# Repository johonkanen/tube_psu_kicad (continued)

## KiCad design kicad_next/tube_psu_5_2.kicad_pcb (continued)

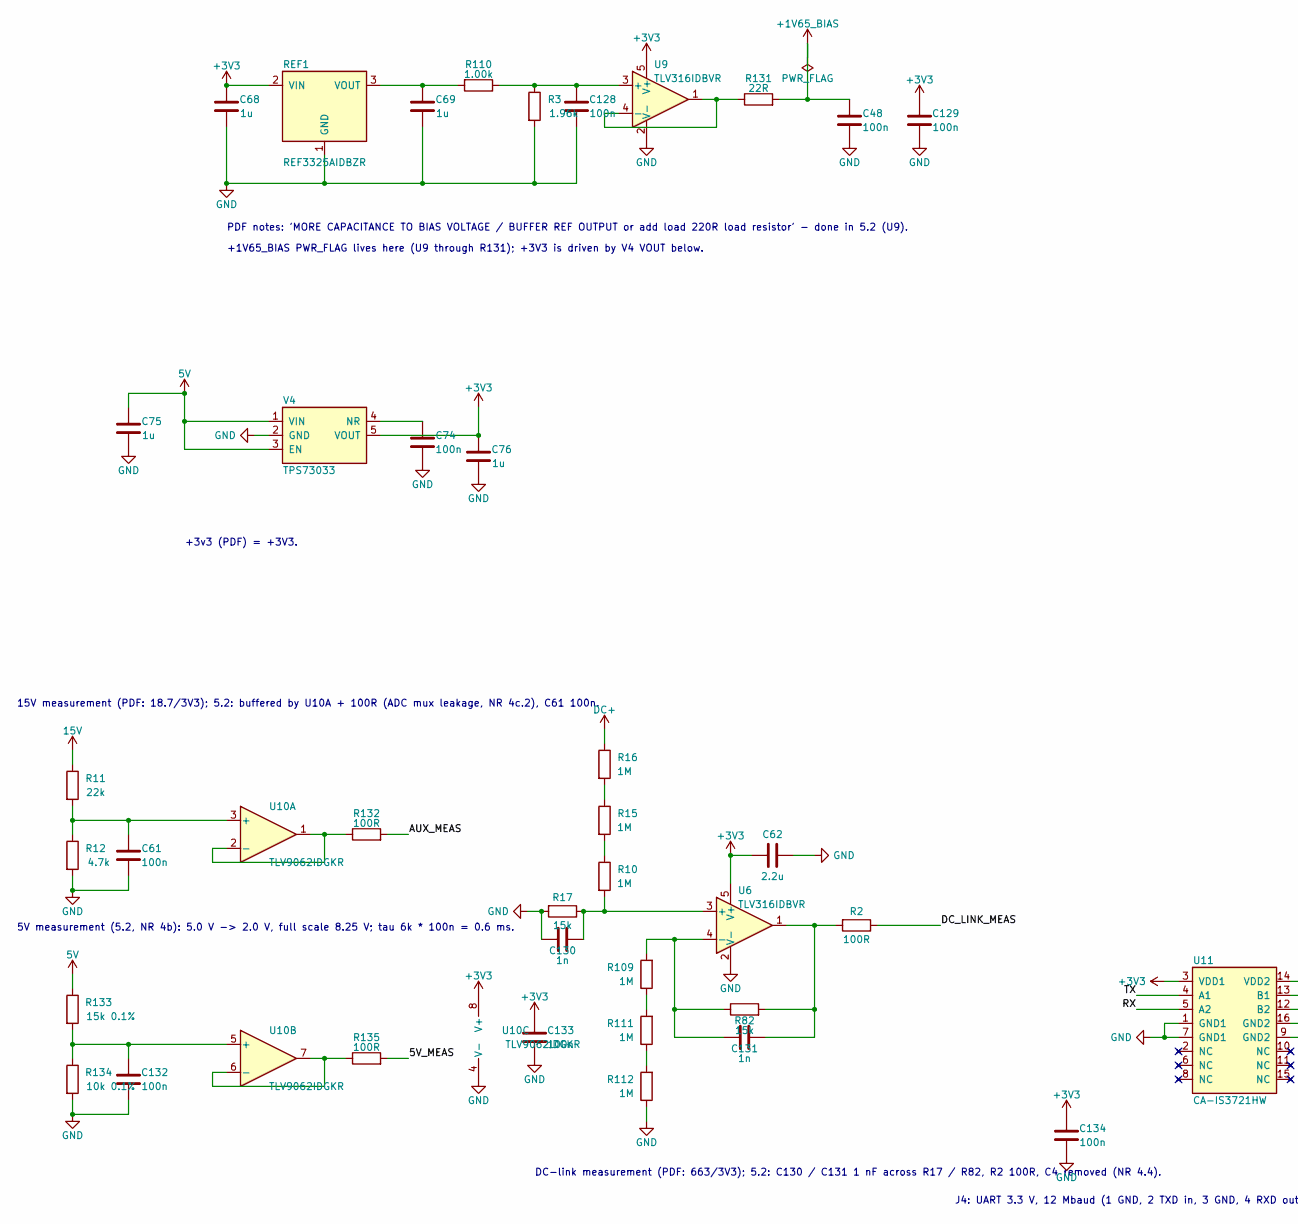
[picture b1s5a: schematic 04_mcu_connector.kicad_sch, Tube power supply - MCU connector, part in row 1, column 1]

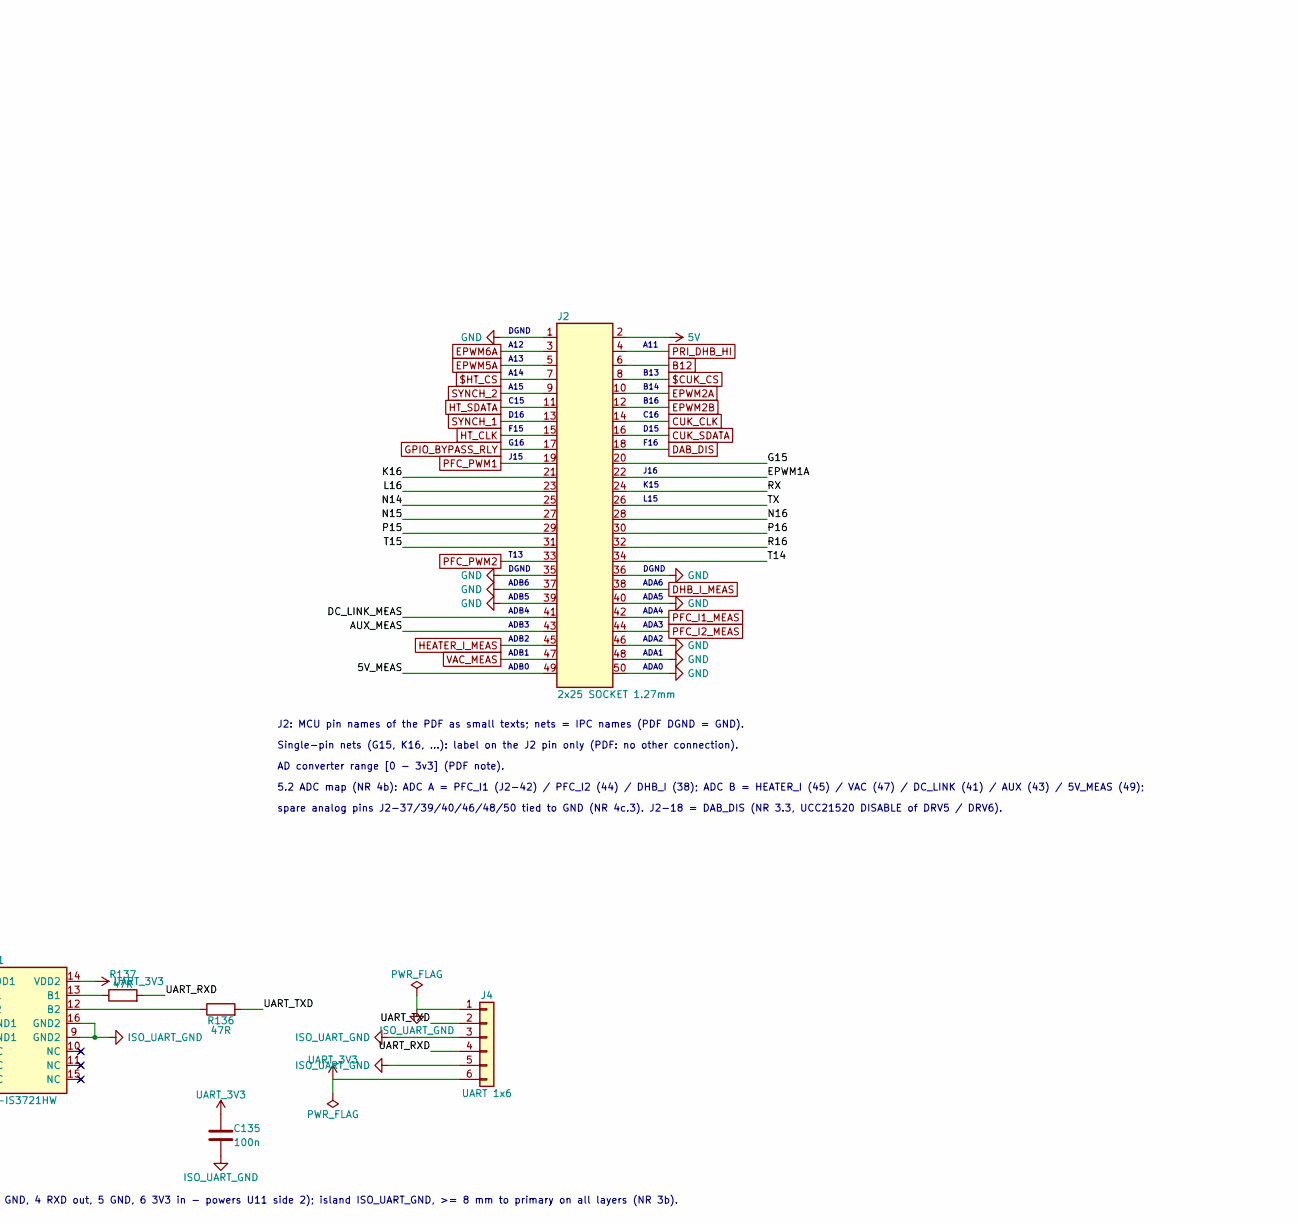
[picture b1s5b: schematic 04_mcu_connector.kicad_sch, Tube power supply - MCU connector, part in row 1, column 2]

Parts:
C48, C61, C74, C128, C129, C132, C133, C134, C135: 100n; C_0603_1608Metric; LCSC C14663
C62: 2.2u; C_0603_1608Metric; LCSC C23630
C68, C69, C75, C76: 1u; C_0603_1608Metric; LCSC C15849
C130, C131: 1n; C_0603_1608Metric; LCSC C106246
J2: 2x25 SOCKET 1.27mm; PinSocket_2x25_P1.27mm_Vertical_XKB_X1321FV; LCSC C2881768
J4: UART 1x6; PinHeader_1x06_P2.54mm_Vertical; LCSC C492405
R2, R132, R135: 100R; R_0603_1608Metric; LCSC C22775
R3: 1.96k; R_0603_1608Metric; LCSC C22854
R10, R15, R16, R111, R112: 1M; R_0805_2012Metric_Pad1.20x1.40mm_HandSolder; LCSC C17514
R11: 22k; R_0603_1608Metric; LCSC C31850
R12: 4.7k; R_0603_1608Metric; LCSC C23162
R17, R82: 15k; R_0603_1608Metric; LCSC C22809
R109: 1M; R_0805_2012Metric_Proteus; LCSC C17514
R110: 1.00k; R_0603_1608Metric; LCSC C21190
R131: 22R; R_0603_1608Metric; LCSC C23345
R133: 15k 0.1%; R_0603_1608Metric; LCSC C318137
R134: 10k 0.1%; R_0603_1608Metric; LCSC C95204
R136, R137: 47R; R_0603_1608Metric; LCSC C23182
REF1: REF3325AIDBZR; SOT-23_Proteus; LCSC C69039
U6: TLV316IDBVR; SOT-23-5_Proteus; LCSC C575578
U9: TLV316IDBVR; SOT-23-5; LCSC C575578
U10: TLV9062IDGKR; VSSOP-8_3x3mm_P0.65mm; LCSC C398356
U11: CA-IS3721HW; SOIC-16W_7.5x10.3mm_P1.27mm_Slot8.0; LCSC C5337993
V4: TPS73033; SOT-23-5_Proteus; LCSC C57424

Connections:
5V: C75.1, J2.2, R133.1, V4.1 (VIN), V4.3 (EN); also elsewhere on the board
15V: R11.1; also elsewhere on the board
$CUK_CS: J2.8; also elsewhere on the board
$HT_CS: J2.7; also elsewhere on the board
+1V65_BIAS: C48.1, R131.2; also elsewhere on the board
+3V3: C62.1, C68.1, C76.1, C129.1, C133.1, C134.1, REF1.2 (VIN), U6.5 (V+), U9.5 (V+), U10.8 (V+), U11.3 (VDD1), V4.5 (VOUT); also elsewhere on the board
/04 MCU connector/5V_MEAS: J2.49, R135.2
/04 MCU connector/AUX_MEAS: J2.43, R132.2
/04 MCU connector/DC_LINK_MEAS: J2.41, R2.1
/04 MCU connector/EPWM1A: J2.22
/04 MCU connector/G15: J2.20
/04 MCU connector/K16: J2.21
/04 MCU connector/L16: J2.23
/04 MCU connector/N14: J2.25
/04 MCU connector/N15: J2.27
/04 MCU connector/N16: J2.28
/04 MCU connector/P15: J2.29
/04 MCU connector/P16: J2.30
/04 MCU connector/R16: J2.32
/04 MCU connector/RX: J2.24, U11.5 (A2)
/04 MCU connector/T14: J2.34
/04 MCU connector/T15: J2.31
/04 MCU connector/TX: J2.26, U11.4 (A1)
/04 MCU connector/UART_RXD: J4.4, R137.2
/04 MCU connector/UART_TXD: J4.2, R136.2
B12: J2.6; also elsewhere on the board
CUK_CLK: J2.14; also elsewhere on the board
CUK_SDATA: J2.16; also elsewhere on the board
DAB_DIS: J2.18; also elsewhere on the board
DC+: R16.1; also elsewhere on the board
DHB_I_MEAS: J2.38; also elsewhere on the board
EPWM2A: J2.10; also elsewhere on the board
EPWM2B: J2.12; also elsewhere on the board
EPWM5A: J2.5; also elsewhere on the board
EPWM6A: J2.3; also elsewhere on the board
GND: C48.2, C61.1, C62.2, C68.2, C69.2, C74.2, C75.2, C76.2, C128.2, C129.2, C130.2, C132.2, C133.2, C134.2, J2.1, J2.35, J2.36, J2.37, J2.39, J2.40, J2.46, J2.48, J2.50, R3.2, R12.2, R17.2, R112.1, R134.2, REF1.1 (GND), U6.2 (V-), U9.2 (V-), U10.4 (V-), U11.1 (GND1), U11.7 (GND1), V4.2 (GND); also elsewhere on the board
GPIO_BYPASS_RLY: J2.17; also elsewhere on the board
HEATER_I_MEAS: J2.45; also elsewhere on the board
HT_CLK: J2.15; also elsewhere on the board
HT_SDATA: J2.11; also elsewhere on the board
ISO_UART_GND: C135.2, J4.1, J4.3, J4.5, U11.9 (GND2), U11.16 (GND2)
unnamed: C131.2, R2.2, R82.2, U6.1
unnamed: R10.1, R15.2
unnamed: R15.1, R16.2
unnamed: R109.1, R111.2
unnamed: R111.1, R112.2
unnamed: C69.1, R110.2, REF1.3 (VOUT)
unnamed: C130.1, R10.2, R17.1, U6.3 (+)
unnamed: C131.1, R82.1, R109.2, U6.4 (-)
unnamed: C128.1, R3.1, R110.1, U9.3 (+)
unnamed: R131.1, U9.1, U9.4 (-)
unnamed: C61.2, R11.2, R12.1, U10.3 (+)
unnamed: R132.1, U10.1, U10.2 (-)
unnamed: C132.1, R133.2, R134.1, U10.5 (+)
unnamed: R135.1, U10.6 (-), U10.7
unnamed: R137.1, U11.13 (B1)
unnamed: R136.1, U11.12 (B2)
unnamed: C74.1, V4.4 (NR)
PFC_I1_MEAS: J2.42; also elsewhere on the board
PFC_I2_MEAS: J2.44; also elsewhere on the board
PFC_PWM1: J2.19; also elsewhere on the board
PFC_PWM2: J2.33; also elsewhere on the board
PRI_DHB_HI: J2.4; also elsewhere on the board
SYNCH_1: J2.13; also elsewhere on the board
SYNCH_2: J2.9; also elsewhere on the board
UART_3V3: C135.1, J4.6, U11.14 (VDD2)
VAC_MEAS: J2.47; also elsewhere on the board

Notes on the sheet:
DGND
A12
A11
A13
A14
B13
A15
B14
C15
B16
D16
C16
F15
D15
G16
F16
J15
J16
K15
L15
T13
ADB6
ADA6
ADB5
ADA5
ADB4
ADA4
ADB3
ADA3
ADB2
ADA2
ADB1
ADA1
ADB0
ADA0
J2: MCU pin names of the PDF as small texts; nets = IPC names (PDF DGND = GND).
Single-pin nets (G15, K16, ...): label on the J2 pin only (PDF: no other connection).
5.2 ADC map (NR 4b): ADC A = PFC_I1 (J2-42) / PFC_I2 (44) / DHB_I (38); ADC B = HEATER_I (45) / VAC (47) / DC_LINK (41) / AUX (43) / 5V_MEAS (49);
spare analog pins J2-37/39/40/46/48/50 tied to GND (NR 4c.3). J2-18 = DAB_DIS (NR 3.3, UCC21520 DISABLE of DRV5 / DRV6).
AD converter range [0 - 3v3] (PDF note).

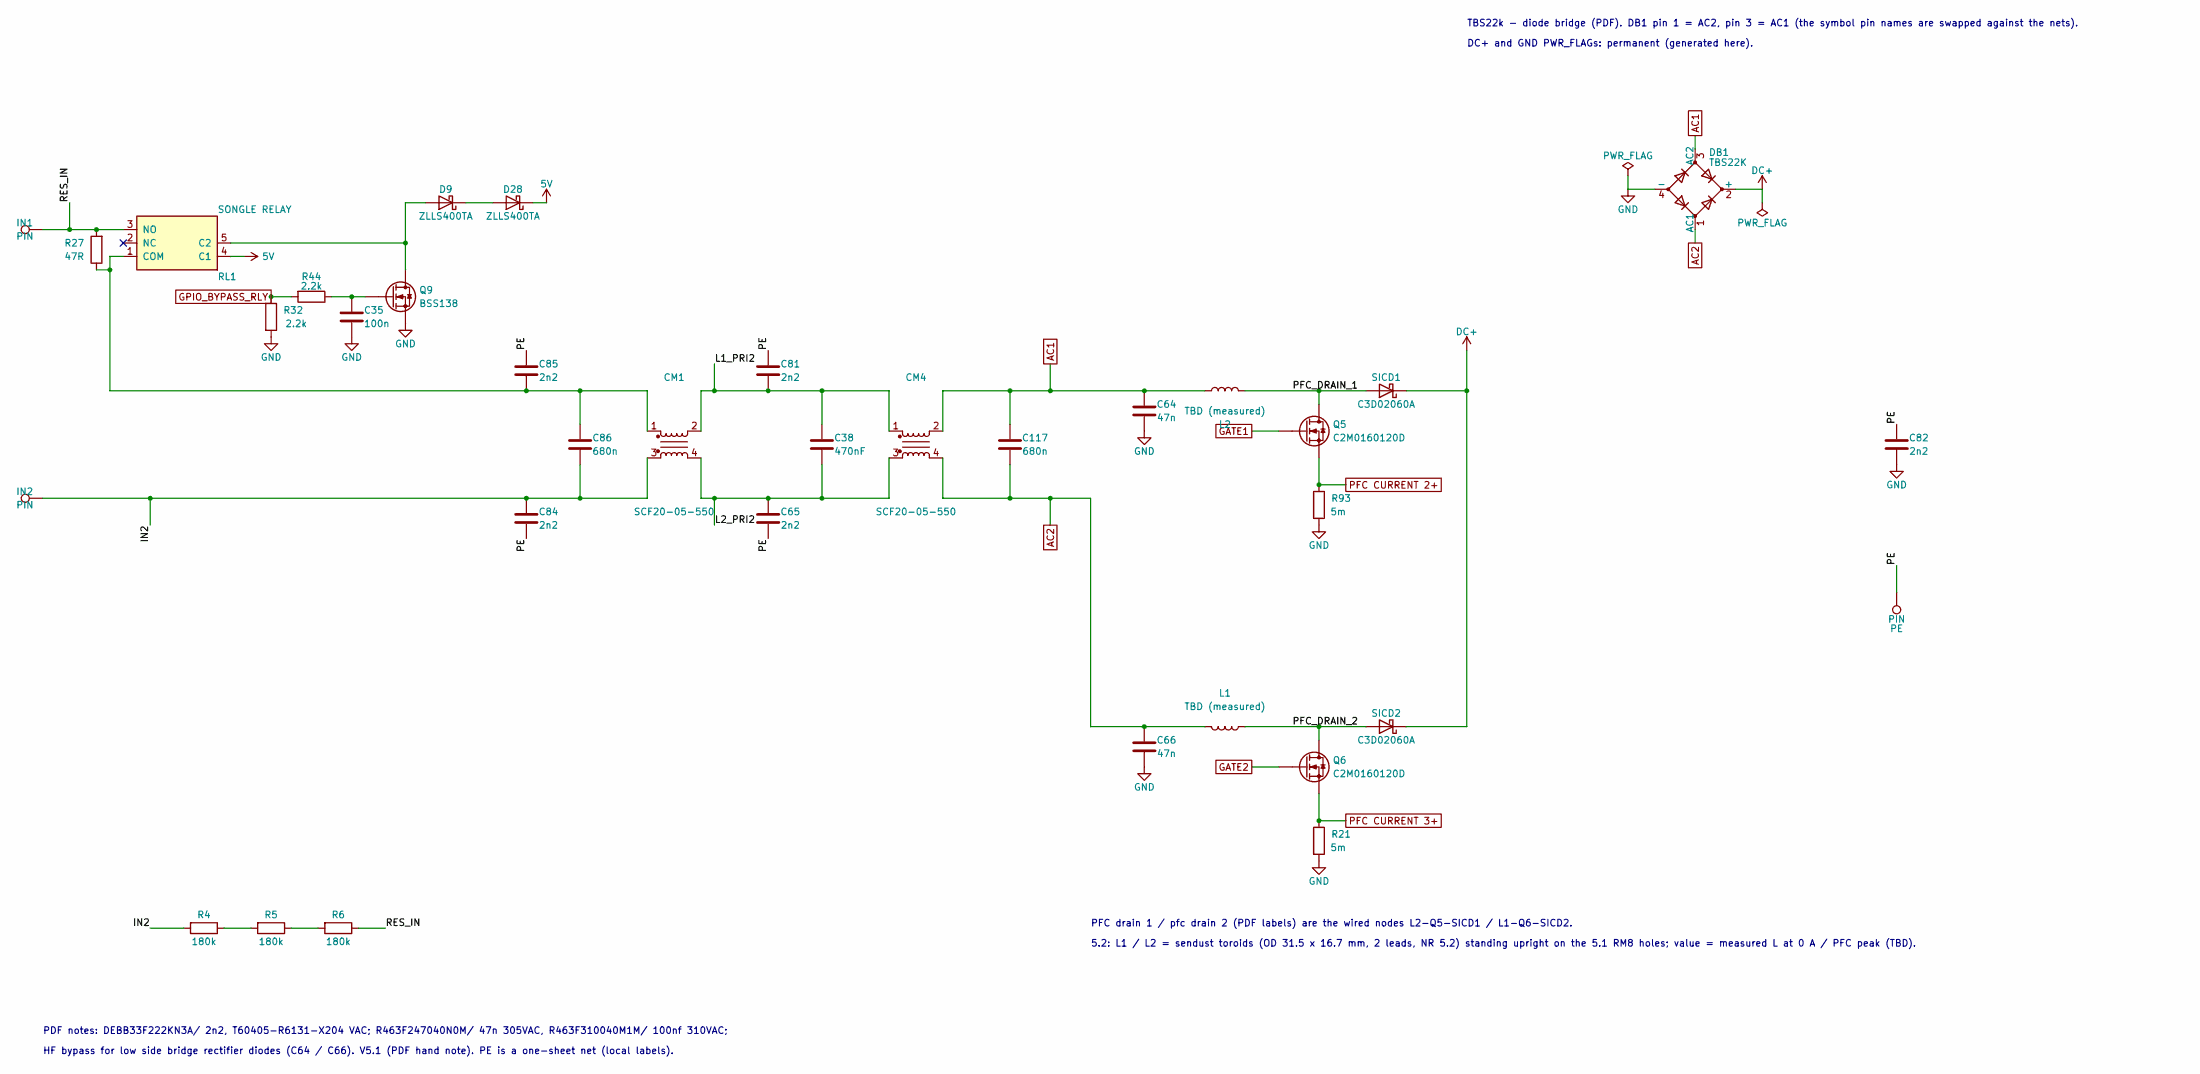
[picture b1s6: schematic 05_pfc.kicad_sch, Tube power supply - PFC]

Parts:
C35: 100n; C_0603_1608Metric; LCSC C14663
C38: 470nF; C_Rect_L26.5mm_W6.0mm_P22.50mm_MKS4; LCSC C3297747
C64, C66: 47n; C_Rect_L13.0mm_W5.0mm_P10.00mm_FKS3_FKP3_MKS4; LCSC C3298405
C65, C81, C82, C84, C85: 2n2; C_Disc_D12.5mm_W5.0mm_P7.50mm; LCSC C96522
C86, C117: 680n; C_Rect_L26.5mm_W11.5mm_P22.50mm_MKS4; LCSC C2888216
CM1, CM4: SCF20-05-550; L_CommonMode_SCF20-05-550; LCSC C1534140
D9, D28: ZLLS400TA; D_SOD-323_AC; LCSC C460267
DB1: TBS22K; D_Bridge_TBS
IN1, IN2: PIN; Terminal_2x1_P5.00mm_D2.0mm_Drill1.4mm
L1: TBD (measured); L_Toroid_D31.5mm_W16.7mm_Vertical_RM8_45deg
L2: TBD (measured); L_Toroid_D31.5mm_W16.7mm_Vertical_RM8_315deg
PE: PIN; Terminal_2x1_P5.00mm_D2.0mm_Drill1.4mm
Q5, Q6: C2M0160120D; TO-247-3_Vertical
Q9: BSS138; SOT-23_Proteus; LCSC C82045
R4, R5, R6: 180k; R_1206_3216Metric; LCSC C17923
R21, R93: 5m; R_0508_1220Metric_KRL2012; LCSC C2073455
R27: 47R; R_Radial_Power_L13.0mm_W9.0mm_P5.00mm
R32, R44: 2.2k; R_0603_1608Metric; LCSC C4190
RL1: SONGLE RELAY; Relay_Songle_SRD_5pin; LCSC C35449
SICD1, SICD2: C3D02060A; TO-220-2_Vertical_KA

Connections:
5V: D28.C (K), RL1.4 (C1); also elsewhere on the board
/05 PFC/IN2: C84.1, C86.2, CM1.3, IN2.1, R4.2
/05 PFC/L1_PRI2: C38.1, C81.1, CM1.2, CM4.1
/05 PFC/L2_PRI2: C38.2, C65.1, CM1.4, CM4.3
/05 PFC/PE: C65.2, C81.2, C82.2, C84.2, C85.2, PE.1
/05 PFC/PFC_DRAIN_1: L2.2, Q5.2 (D), SICD1.A
/05 PFC/PFC_DRAIN_2: L1.1, Q6.2 (D), SICD2.A
/05 PFC/RES_IN: IN1.1, R6.1, R27.2, RL1.3 (NO)
AC1: C64.1, C117.1, CM4.2, DB1.3 (AC2), L2.1; also elsewhere on the board
AC2: C66.1, C117.2, CM4.4, DB1.1 (AC1), L1.2; also elsewhere on the board
DC+: DB1.2 (+), SICD1.K, SICD2.K; also elsewhere on the board
GATE1: Q5.1 (G); also elsewhere on the board
GATE2: Q6.1 (G); also elsewhere on the board
GND: C35.2, C64.2, C66.2, C82.1, DB1.4 (-), Q9.3 (S), R21.2, R32.2, R93.2; also elsewhere on the board
GPIO_BYPASS_RLY: R32.1, R44.2; also elsewhere on the board
unnamed: D9.C (K), D28.A
unnamed: D9.A, Q9.1 (D), RL1.5 (C2)
unnamed: C35.1, Q9.2 (G), R44.1
unnamed: R4.1, R5.2
unnamed: R5.1, R6.2
unnamed: C85.1, C86.1, CM1.1, R27.1, RL1.1 (COM)
PFC CURRENT 2+: Q5.3 (S), R93.1; also elsewhere on the board
PFC CURRENT 3+: Q6.3 (S), R21.1; also elsewhere on the board

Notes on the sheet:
PFC drain 1 / pfc drain 2 (PDF labels) are the wired nodes L2-Q5-SICD1 / L1-Q6-SICD2.
5.2: L1 / L2 = sendust toroids (OD 31.5 x 16.7 mm, 2 leads, NR 5.2) standing upright on the 5.1 RM8 holes; value = measured L at 0 A / PFC peak (TBD).
TBS22k - diode bridge (PDF). DB1 pin 1 = AC2, pin 3 = AC1 (the symbol pin names are swapped against the nets).
DC+ and GND PWR_FLAGs: permanent (generated here).
PDF notes: DEBB33F222KN3A/ 2n2, T60405-R6131-X204 VAC; R463F247040N0M/ 47n 305VAC, R463F310040M1M/ 100nf 310VAC;
HF bypass for low side bridge rectifier diodes (C64 / C66). V5.1 (PDF hand note). PE is a one-sheet net (local labels).

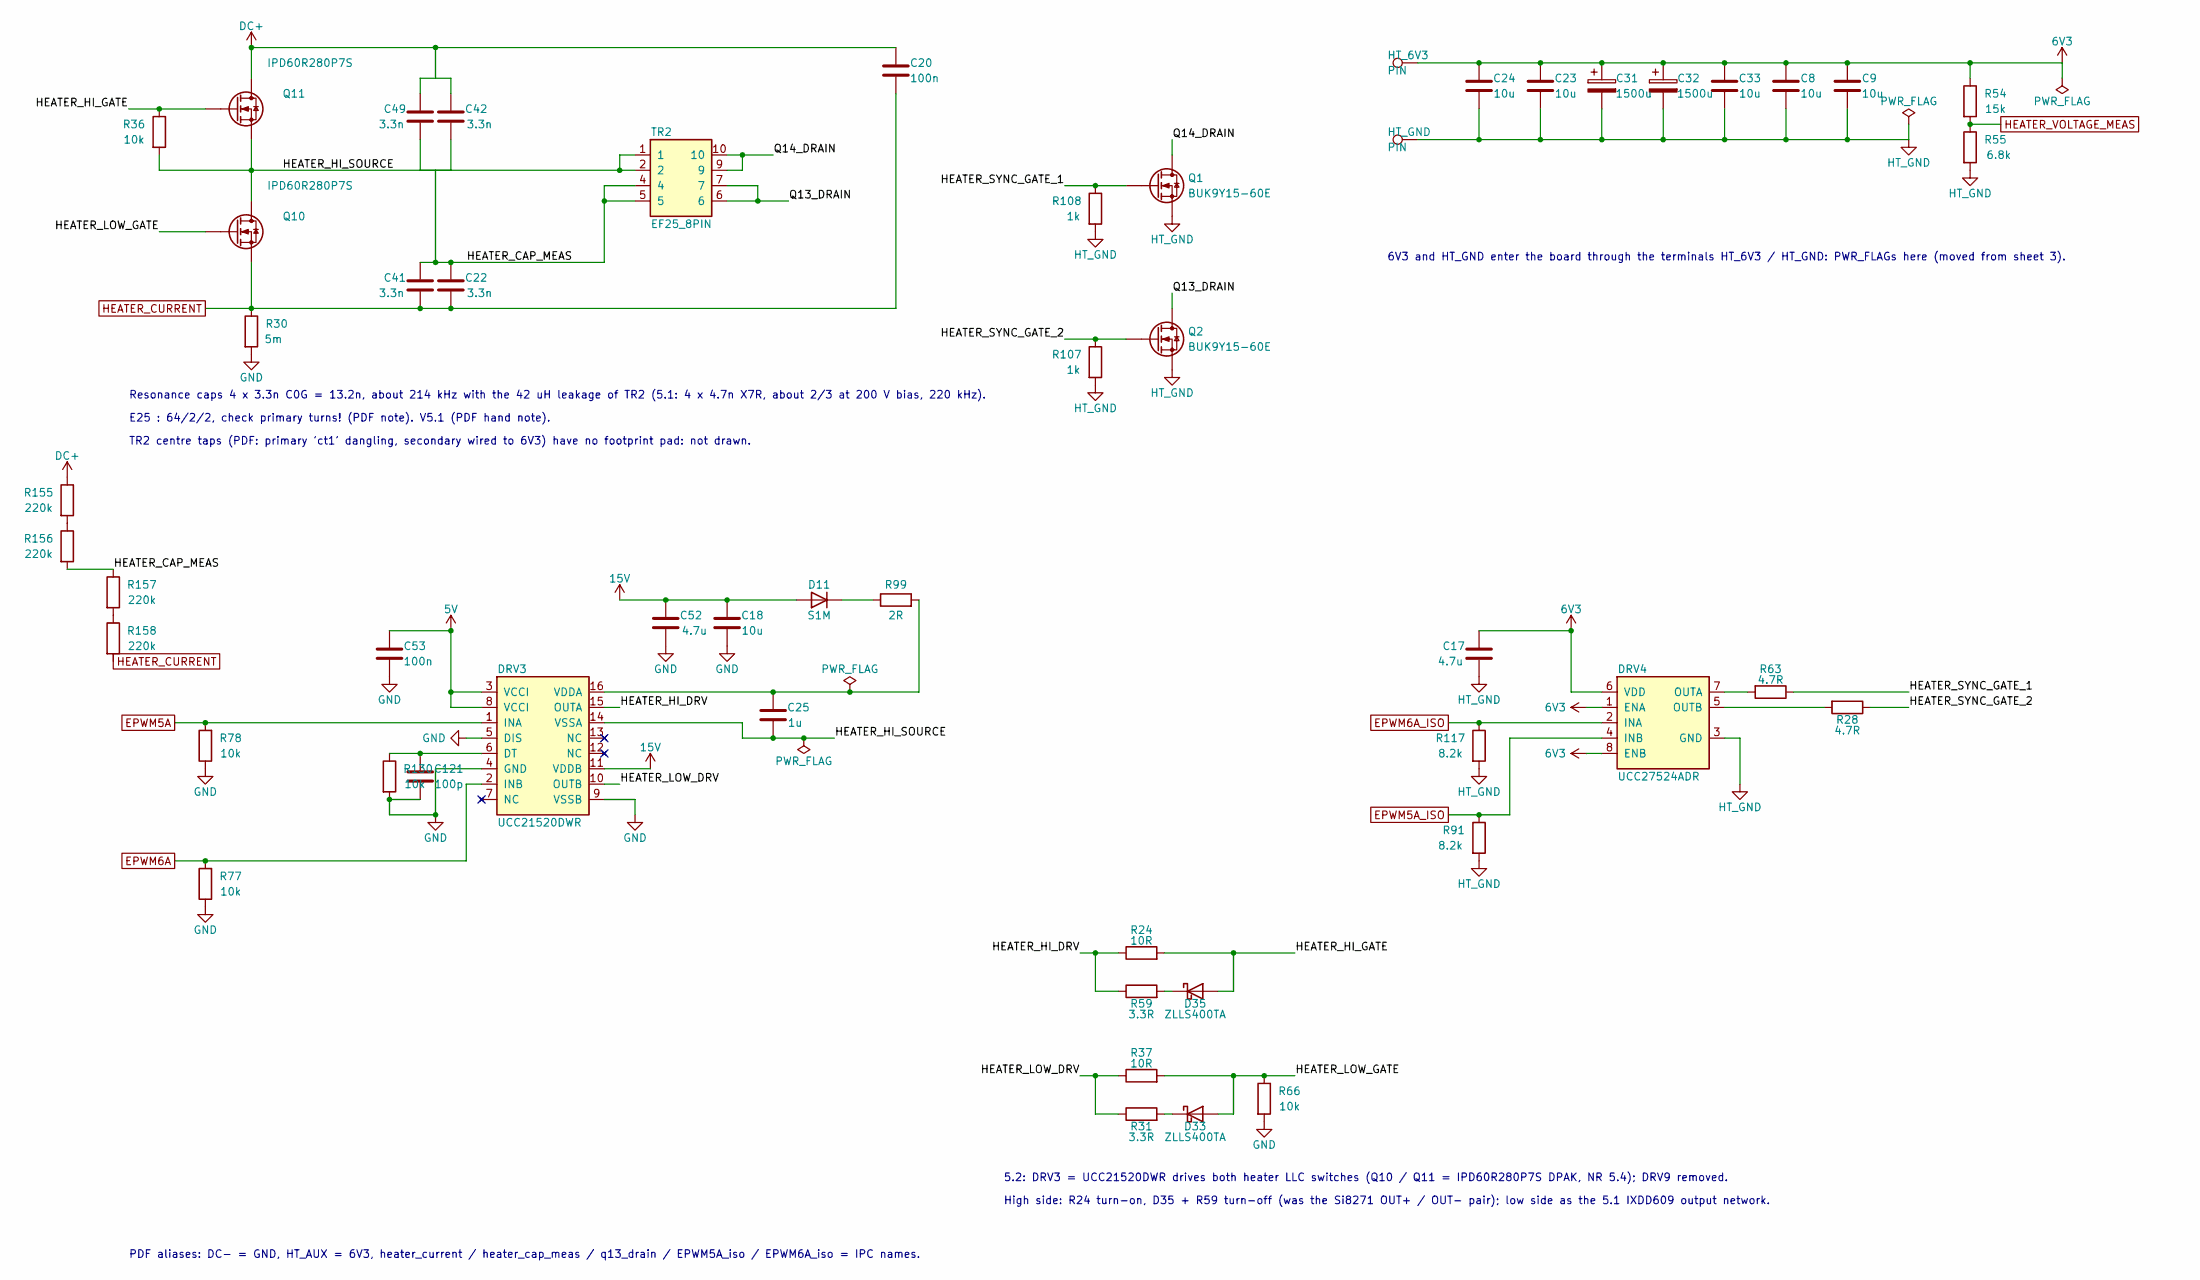
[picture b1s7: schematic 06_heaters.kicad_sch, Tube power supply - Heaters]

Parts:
C8, C9, C18, C23, C24, C33: 10u; C_1206_3216Metric_Pad1.33x1.80mm_HandSolder; LCSC C13585
C17, C52: 4.7u; C_0603_1608Metric; LCSC C6119856
C20: 100n; C_1210_3225Metric; LCSC C692295
C22, C41, C42, C49: 3.3n; C_1206_3216Metric; LCSC C105987
C25: 1u; C_1206_3216Metric_Proteus3.15; LCSC C1848
C31, C32: 1500u; CP_Radial_D8.0mm_P3.50mm_H20mm; LCSC C432399
C53: 100n; C_0603_1608Metric; LCSC C14663
C121: 100p; C_0603_1608Metric; LCSC C14858
D11: S1M; D_SMA_AC; LCSC C64915
D33, D35: ZLLS400TA; D_SOD-323_AC; LCSC C460267
DRV3: UCC21520DWR; SOIC-16W_7.5x10.3mm_P1.27mm; LCSC C601651
DRV4: UCC27524ADR; SOIC-8_3.9x4.9mm_P1.27mm; LCSC C185857
HT_6V3: PIN; Terminal_2x1_P5.00mm_D2.0mm_Drill1.4mm
HT_GND: PIN; Terminal_2x1_P5.00mm_D2.0mm_Drill1.4mm
Q1, Q2: BUK9Y15-60E; LFPAK56_Proteus; LCSC C458196
Q10, Q11: IPD60R280P7S; TO-252-2; LCSC C536813
R24: 10R; R_1206_3216Metric; LCSC C17903
R28, R63: 4.7R; R_0805_2012Metric_Proteus2.13; LCSC C17675
R30: 5m; R_0508_1220Metric_KRL2012; LCSC C2073455
R31: 3.3R; R_0805_2012Metric_Pad1.20x1.40mm_HandSolder; LCSC C22356719
R36, R66, R77, R78, R130: 10k; R_0603_1608Metric; LCSC C25804
R37: 10R; R_0805_2012Metric_Pad1.20x1.40mm_HandSolder; LCSC C17415
R54: 15k; R_0603_1608Metric; LCSC C22809
R55: 6.8k; R_0603_1608Metric; LCSC C23212
R59: 3.3R; R_1206_3216Metric; LCSC C2930397
R91, R117: 8.2k; R_0603_1608Metric; LCSC C25981
R99: 2R; R_1206_3216Metric; LCSC C2907381
R107, R108: 1k; R_0603_1608Metric; LCSC C21190
R155, R156, R157, R158: 220k; R_1206_3216Metric; LCSC C17956
TR2: EF25_8PIN; Transformer_EF25_2x5_P5.08mm_8pin

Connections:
5V: C53.1, DRV3.3 (VCCI), DRV3.8 (VCCI); also elsewhere on the board
6V3: C8.1, C9.1, C17.1, C23.1, C24.1, C31.1, C32.1, C33.1, DRV4.1 (ENA), DRV4.6 (VDD), DRV4.8 (ENB), HT_6V3.1, R54.1; also elsewhere on the board
15V: C18.1, C52.1, D11.A, DRV3.11 (VDDB); also elsewhere on the board
/06 Heaters/HEATER_CAP_MEAS: C22.1, C41.1, C42.2, C49.2, R156.2, R157.1, TR2.4, TR2.5
/06 Heaters/HEATER_HI_DRV: DRV3.15 (OUTA), R24.1, R59.1
/06 Heaters/HEATER_HI_GATE: D35.A, Q11.1 (G), R24.2, R36.1
/06 Heaters/HEATER_HI_SOURCE: C25.2, DRV3.14 (VSSA), Q10.2 (D), Q11.3 (S), R36.2, TR2.1, TR2.2
/06 Heaters/HEATER_LOW_DRV: DRV3.10 (OUTB), R31.1, R37.1
/06 Heaters/HEATER_LOW_GATE: D33.A, Q10.1 (G), R37.2, R66.1
/06 Heaters/HEATER_SYNC_GATE_1: Q1.2 (G), R63.1, R108.1
/06 Heaters/HEATER_SYNC_GATE_2: Q2.2 (G), R28.1, R107.1
/06 Heaters/Q13_DRAIN: Q2.3 (D), TR2.6, TR2.7; also elsewhere on the board
/06 Heaters/Q14_DRAIN: Q1.3 (D), TR2.9, TR2.10; also elsewhere on the board
DC+: C20.1, C42.1, C49.1, Q11.2 (D), R155.1; also elsewhere on the board
EPWM5A: DRV3.1 (INA), R78.2; also elsewhere on the board
EPWM5A_ISO: DRV4.4 (INB), R91.1; also elsewhere on the board
EPWM6A: DRV3.2 (INB), R77.2; also elsewhere on the board
EPWM6A_ISO: DRV4.2 (INA), R117.1; also elsewhere on the board
GND: C18.2, C52.2, C53.2, C121.2, DRV3.4 (GND), DRV3.5 (DIS), DRV3.9 (VSSB), R30.2, R66.2, R77.1, R78.1, R130.2; also elsewhere on the board
HEATER_CURRENT: C20.2, C22.2, C41.2, Q10.3 (S), R30.1, R158.2; also elsewhere on the board
HEATER_VOLTAGE_MEAS: R54.2, R55.1; also elsewhere on the board
HT_GND: C8.2, C9.2, C17.2, C23.2, C24.2, C31.2, C32.2, C33.2, DRV4.3 (GND), HT_GND.1, Q1.1 (S), Q2.1 (S), R55.2, R91.2, R107.2, R108.2, R117.2; also elsewhere on the board
unnamed: D11.C (K), R99.1
unnamed: D33.C (K), R31.2
unnamed: D35.C (K), R59.2
unnamed: C121.1, DRV3.6 (DT), R130.1
unnamed: C25.1, DRV3.16 (VDDA), R99.2
unnamed: DRV4.7 (OUTA), R63.2
unnamed: DRV4.5 (OUTB), R28.2
unnamed: R155.2, R156.1
unnamed: R157.2, R158.1

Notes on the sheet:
Resonance caps 4 x 3.3n C0G = 13.2n, about 214 kHz with the 42 uH leakage of TR2 (5.1: 4 x 4.7n X7R, about 2/3 at 200 V bias, 220 kHz).
E25 : 64/2/2, check primary turns! (PDF note). V5.1 (PDF hand note).
TR2 centre taps (PDF: primary 'ct1' dangling, secondary wired to 6V3) have no footprint pad: not drawn.
6V3 and HT_GND enter the board through the terminals HT_6V3 / HT_GND: PWR_FLAGs here (moved from sheet 3).
5.2: DRV3 = UCC21520DWR drives both heater LLC switches (Q10 / Q11 = IPD60R280P7S DPAK, NR 5.4); DRV9 removed.
High side: R24 turn-on, D35 + R59 turn-off (was the Si8271 OUT+ / OUT- pair); low side as the 5.1 IXDD609 output network.
PDF aliases: DC- = GND, HT_AUX = 6V3, heater_current / heater_cap_meas / q13_drain / EPWM5A_iso / EPWM6A_iso = IPC names.

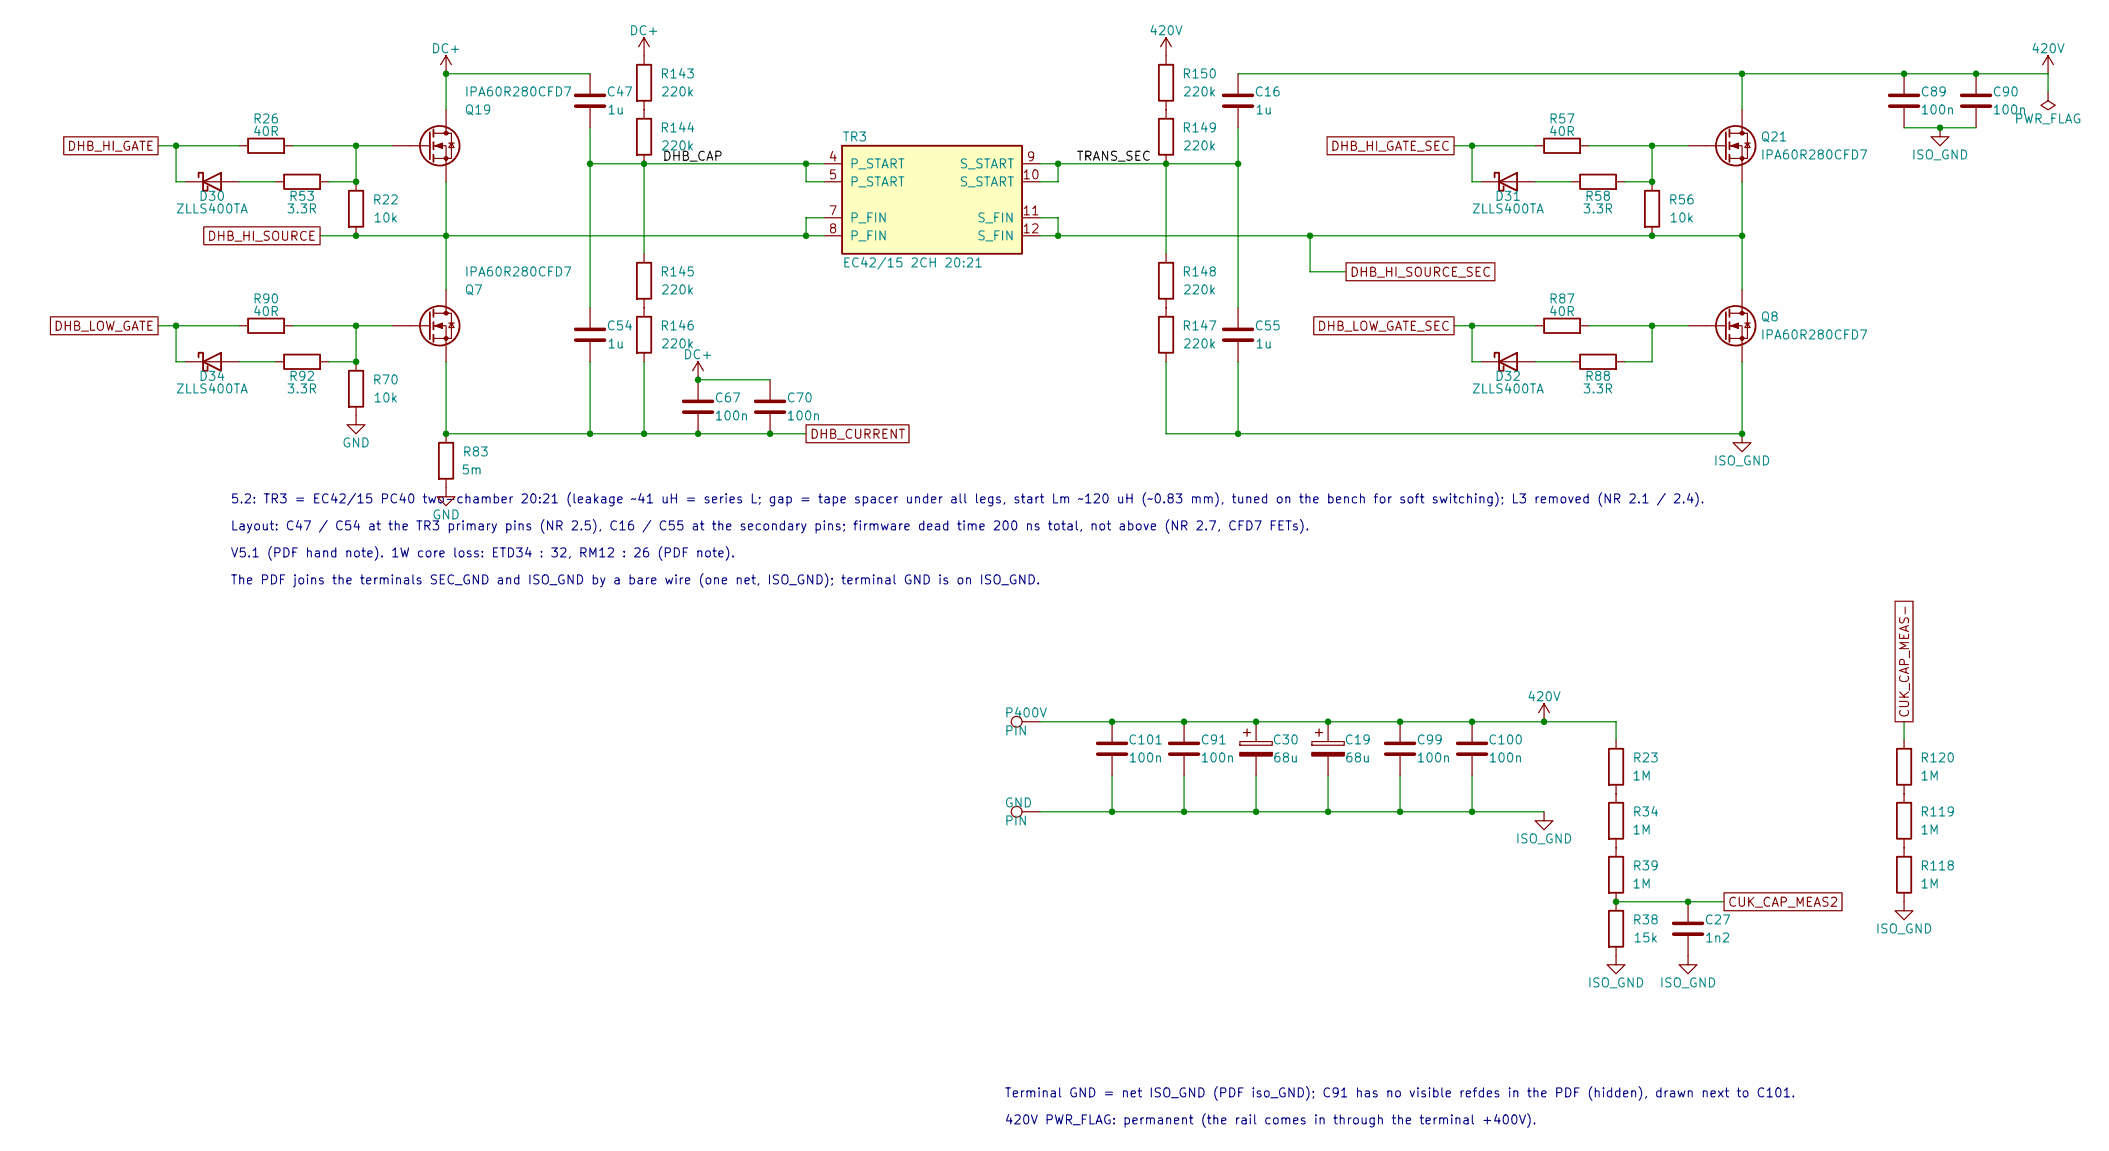
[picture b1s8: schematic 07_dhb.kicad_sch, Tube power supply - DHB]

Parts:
C16, C47, C54, C55: 1u; C_2220_5750Metric_Pad1.97x5.40mm_HandSolder; LCSC C784102
C19, C30: 68u; CP_Radial_D10.0mm_P5.00mm_H50mm; LCSC C913388
C27: 1n2; C_0603_1608Metric; LCSC C576816
C67, C70, C89, C90, C91, C99, C100, C101: 100n; C_1210_3225Metric; LCSC C692295
D30, D31, D32, D34: ZLLS400TA; D_SOD-323_AC; LCSC C460267
GND: PIN; Terminal_2x1_P5.00mm_D2.0mm_Drill1.4mm
P400V: PIN; Terminal_2x1_P5.00mm_D2.0mm_Drill1.4mm
Q7, Q8, Q19, Q21: IPA60R280CFD7; TO-220-3_Vertical
R22, R56, R70: 10k; R_0603_1608Metric; LCSC C25804
R23, R34, R39, R118, R119, R120: 1M; R_0805_2012Metric_Pad1.20x1.40mm_HandSolder; LCSC C17514
R26, R57, R87, R90: 40R; R_0805_2012Metric_Pad1.20x1.40mm_HandSolder; LCSC C2933439
R38: 15k; R_0603_1608Metric; LCSC C22809
R53, R58, R92: 3.3R; R_0805_2012Metric_Pad1.20x1.40mm_HandSolder; LCSC C22356719
R83: 5m; R_0508_1220Metric_KRL2012; LCSC C2073455
R88: 3.3R; R_0805_2012Metric_Proteus; LCSC C22356719
R143, R144, R145, R146, R147, R148, R149, R150: 220k; R_1206_3216Metric; LCSC C17956
TR3: EC42/15 2CH 20:21; Transformer_EC42x15_2Slot_2x8_P5mm

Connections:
420V: C16.1, C19.1, C30.1, C89.1, C90.1, C91.1, C99.1, C100.1, C101.1, P400V.1, Q21.2 (D), R23.1, R150.2
/07 DHB/DHB_CAP: C47.2, C54.1, R144.2, R145.1, TR3.4 (P_START), TR3.5 (P_START)
/07 DHB/TRANS_SEC: C16.2, C55.1, R148.2, R149.1, TR3.9 (S_START), TR3.10 (S_START)
CUK_CAP_MEAS2: C27.2, R38.1, R39.2; also elsewhere on the board
CUK_CAP_MEAS-: R120.2; also elsewhere on the board
DC+: C47.1, C67.1, C70.1, Q19.2 (D), R143.1; also elsewhere on the board
DHB_CURRENT: C54.2, C67.2, C70.2, Q7.3 (S), R83.1, R146.2; also elsewhere on the board
DHB_HI_GATE: D30.C (K), R26.1; also elsewhere on the board
DHB_HI_GATE_SEC: D31.C (K), R57.1; also elsewhere on the board
DHB_HI_SOURCE: Q7.2 (D), Q19.3 (S), R22.2, TR3.7 (P_FIN), TR3.8 (P_FIN); also elsewhere on the board
DHB_HI_SOURCE_SEC: Q8.2 (D), Q21.3 (S), R56.2, TR3.11 (S_FIN), TR3.12 (S_FIN); also elsewhere on the board
DHB_LOW_GATE: D34.C (K), R90.1; also elsewhere on the board
DHB_LOW_GATE_SEC: D32.C (K), R87.1; also elsewhere on the board
GND: R70.2, R83.2; also elsewhere on the board
ISO_GND: C19.2, C27.1, C30.2, C55.2, C89.2, C90.2, C91.2, C99.2, C100.2, C101.2, GND.1, Q8.3 (S), R38.2, R118.1, R147.1; also elsewhere on the board
unnamed: D30.A, R53.1
unnamed: D31.A, R58.1
unnamed: D32.A, R88.1
unnamed: D34.A, R92.1
unnamed: Q7.1 (G), R70.1, R90.2, R92.2
unnamed: Q8.1 (G), R87.2, R88.2
unnamed: Q19.1 (G), R22.1, R26.2, R53.2
unnamed: Q21.1 (G), R56.1, R57.2, R58.2
unnamed: R23.2, R34.1
unnamed: R34.2, R39.1
unnamed: R118.2, R119.1
unnamed: R119.2, R120.1
unnamed: R143.2, R144.1
unnamed: R145.2, R146.1
unnamed: R147.2, R148.1
unnamed: R149.2, R150.1

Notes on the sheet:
V5.1 (PDF hand note). 1W core loss: ETD34 : 32, RM12 : 26 (PDF note).
5.2: TR3 = EC42/15 PC40 two-chamber 20:21 (leakage ~41 uH = series L; gap = tape spacer under all legs, start Lm ~120 uH (~0.83 mm), tuned on the bench for soft switching); L3 removed (NR 2.1 / 2.4).
Layout: C47 / C54 at the TR3 primary pins (NR 2.5), C16 / C55 at the secondary pins; firmware dead time 200 ns total, not above (NR 2.7, CFD7 FETs).
The PDF joins the terminals SEC_GND and ISO_GND by a bare wire (one net, ISO_GND); terminal GND is on ISO_GND.
Terminal GND = net ISO_GND (PDF iso_GND); C91 has no visible refdes in the PDF (hidden), drawn next to C101.
420V PWR_FLAG: permanent (the rail comes in through the terminal +400V).

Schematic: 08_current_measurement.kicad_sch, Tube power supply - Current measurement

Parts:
C10, C26: na; C_0603_1608Metric; not fitted
C11, C123: 5.6p; C_0603_1608Metric; LCSC C1674
C63, C122: 12p; C_0603_1608Metric; LCSC C38523
C124: 100n; C_0603_1608Metric; LCSC C14663
C125: 1u; C_0603_1608Metric; LCSC C15849
R29, R101, R104, R106: 330R; R_0603_1608Metric; LCSC C23138
R35: 33R; R_0603_1608Metric; LCSC C23140
R42: 33; R_0603_1608Metric; LCSC C23140
R89, R103: 33k; R_0603_1608Metric; LCSC C4216
R102, R105: 15k; R_0603_1608Metric; LCSC C22809
U1: LMH6643; TSSOP-8_3x3mm_P0.65mm; LCSC C478382

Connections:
+1V65_BIAS: C122.1, C123.1, R103.2, R105.1; also elsewhere on the board
+3V3: C124.1, C125.1, U1.8 (V+); also elsewhere on the board
DHB_CURRENT: R104.2; also elsewhere on the board
DHB_I_MEAS: C26.2, R42.2; also elsewhere on the board
GND: C10.1, C26.1, C124.2, C125.2, R29.2, R101.2, U1.4 (V-); also elsewhere on the board
HEATER_CURRENT: R106.2; also elsewhere on the board
HEATER_I_MEAS: C10.2, R35.2; also elsewhere on the board
unnamed: C11.1, R35.1, R89.1, U1.1
unnamed: C63.1, R42.1, R102.1, U1.7
unnamed: C123.2, R103.1, R106.1, U1.3 (+)
unnamed: C11.2, R29.1, R89.2, U1.2 (-)
unnamed: C122.2, R104.1, R105.2, U1.5 (+)
unnamed: C63.2, R101.1, R102.2, U1.6 (-)

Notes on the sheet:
C10 / C26 value 'na' (not assembled) in Proteus, pads in the layout. PDF terminals DC- = GND.
2k = 22k||2.2k (PDF hand note).
5.2: shunts 5 mOhm (KRL2012E-M-R005, 2026-11-24): DHB_I 4.40 A/V, HEATER_I 2.00 A/V around +1V65_BIAS (was 5.50 / 2.50 A/V at 4 mOhm).
LMH6643 Vos <= 5 mV (7 mV over temperature) = 1.0 A (1.4 A) on 5 mOhm: zero-current offset calibrated at start-up (firmware).
ESL caps C63 / C122, C11 / C123 sized for 4 mOhm: about 25 % over-compensated with 5 mOhm - tune on the bench.

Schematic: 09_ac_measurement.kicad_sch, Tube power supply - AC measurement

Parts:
C60: 2u2; C_0603_1608Metric; LCSC C23630
C79, C80: 4.7u; C_0603_1608Metric; LCSC C6119856
C126, C127: 1n; C_0603_1608Metric; LCSC C106246
DRV1, DRV2: UCC27511ADBVR; SOT-23-6; LCSC C2676982
R1, R14, R19, R20: 5R; R_1206_3216Metric; LCSC C2999547
R7, R43, R69, R71: 10k; R_0603_1608Metric; LCSC C25804
R47, R48, R50, R51, R52: 1M; R_0805_2012Metric_Pad1.20x1.40mm_HandSolder; LCSC C17514
R49, R80: 12k; R_0603_1608Metric; LCSC C22790
R65: 100R; R_0603_1608Metric; LCSC C22775
R79: 1M; R_0805_2012Metric_Proteus; LCSC C17514
U8: TLV316IDBVR; SOT-23-5_Proteus; LCSC C575578

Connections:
15V: C79.1, C80.1, DRV1.1 (VDD), DRV2.1 (VDD); also elsewhere on the board
+1V65_BIAS: C126.1, R80.1; also elsewhere on the board
+3V3: C60.1, U8.5 (V+); also elsewhere on the board
AC1: R47.1; also elsewhere on the board
AC2: R50.1; also elsewhere on the board
GATE1: R1.2, R14.2, R43.2; also elsewhere on the board
GATE2: R7.2, R19.2, R20.2; also elsewhere on the board
GND: C60.2, C79.2, C80.2, DRV1.4 (GND), DRV1.5 (IN-), DRV2.4 (GND), DRV2.5 (IN-), R7.1, R43.1, R69.1, R71.1, U8.2 (V-); also elsewhere on the board
unnamed: C127.1, R49.1, R65.2, U8.1
unnamed: DRV1.2 (OUTH), R14.1
unnamed: DRV1.3 (OUTL), R1.1
unnamed: DRV2.2 (OUTH), R20.1
unnamed: DRV2.3 (OUTL), R19.1
unnamed: R47.2, R48.1
unnamed: R48.2, R79.1
unnamed: R50.2, R51.1
unnamed: R51.2, R52.1
unnamed: C126.2, R52.2, R80.2, U8.3 (+)
unnamed: C127.2, R49.2, R79.2, U8.4 (-)
PFC_PWM1: DRV1.6 (IN+), R71.2; also elsewhere on the board
PFC_PWM2: DRV2.6 (IN+), R69.2; also elsewhere on the board
VAC_MEAS: R65.1; also elsewhere on the board

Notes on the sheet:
PDF labels pfc_pwm1/2, gate1/2 = nets PFC_PWM1/2, GATE1/2.
5.2: R49 / R80 15k -> 12k (gain 0.004, no clipping up to 264 Vrms, NR 4.3), C126 / C127 1 nF C0G across R80 / R49 (NR 4.2); no output cap (ADC mux).

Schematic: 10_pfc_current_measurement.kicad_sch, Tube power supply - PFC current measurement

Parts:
C77, C88: 100p; C_0603_1608Metric; LCSC C14858
C87: 1u; C_0603_1608Metric; LCSC C15849
C106, C107, C112, C113: 20p; C_0603_1608Metric; LCSC C1648
R33, R62, R94, R97: 330R; R_0603_1608Metric; LCSC C23138
R60, R95, R98, R100: 6.8k; R_0603_1608Metric; LCSC C23212
R61, R96: 100; R_0603_1608Metric; LCSC C22775
U4: LMH6643; TSSOP-8_3x3mm_P0.65mm; LCSC C478382

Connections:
+1V65_BIAS: C106.1, C107.1, R60.1, R100.2; also elsewhere on the board
+3V3: C87.1, U4.8 (V+); also elsewhere on the board
GND: C77.2, C87.2, C88.2, R94.2, R97.2, U4.4 (V-); also elsewhere on the board
unnamed: C112.1, R61.2, R95.1, U4.7
unnamed: C113.1, R96.2, R98.1, U4.1
unnamed: C106.2, R33.1, R60.2, U4.3 (+)
unnamed: C113.2, R97.1, R98.2, U4.2 (-)
unnamed: C107.2, R62.1, R100.1, U4.5 (+)
unnamed: C112.2, R94.1, R95.2, U4.6 (-)
PFC CURRENT 2+: R33.2; also elsewhere on the board
PFC CURRENT 3+: R62.2; also elsewhere on the board
PFC_I1_MEAS: C88.1, R96.1; also elsewhere on the board
PFC_I2_MEAS: C77.1, R61.1; also elsewhere on the board

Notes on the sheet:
2k = 22k||2.2k (PDF hand note, twice on the page).
5.2: legs already balanced (C113 / C106, C112 / C107 20p): tau = 6.8k * 20p = 136 ns ~ 0.54 nH / 4 mOhm (NR 4.11); offset calibrated (LMH6643 Vos).
Shunts R93 / R21 5 mOhm (KRL2012E-M-R005, 2026-11-24): PFC_I1 / PFC_I2 9.71 A/V around +1V65_BIAS (was 12.13 A/V at 4 mOhm), range about -15.5 / +15.7 A.

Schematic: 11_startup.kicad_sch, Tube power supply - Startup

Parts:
C14: 4.7u; C_1206_3216Metric_Pad1.33x1.80mm_HandSolder; LCSC C29823
C28, C37, C56: 82u 450V; CP_Radial_D12.5mm_P5.00mm_Proteus_H45mm; LCSC C51890374
C29: 82u 450V; CP_Radial_D12.5mm_P5.00mm_H45mm; LCSC C51890374
C73: 2.2u; C_2220_5750Metric_Pad1.97x5.40mm_HandSolder; LCSC C445674

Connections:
15V: C14.1; also elsewhere on the board
DC+: C28.1, C29.1, C37.1, C56.1, C73.1; also elsewhere on the board
GND: C14.2, C28.2, C29.2, C37.2, C56.2, C73.2; also elsewhere on the board

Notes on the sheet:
Bulk capacitors of the DC link (C29/C56/C28/C37: EEE-FTE221XAP note in the PDF). 5.2: Man Yue ERT 82 uF 450 V (NR 5.2b).
PDF terminal DC- = net GND. PWR_FLAGs: 15V on sheet 1 (AUX supply), DC+ and GND on sheet 5 (bridge DB1).
The PDF page also wires the terminals HT_AUX and 6V3 together: HT_AUX is an alias of the 6V3 net (no part here).
